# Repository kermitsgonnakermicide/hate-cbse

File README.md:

# hate-cbse
A desk-sized CoreXY pen plotter with a custom RP2350 based motherboard!

# why? 
### just why?
- i come from the great country of India, and as a result of that I'm in CBSE [(Central Board of Secondary Education)](https://www.cbse.gov.in/)
- CBSE, being a central board(for the entire country) and in general being decades behind other boards/methods has some quirky little requirements which seem utterly useless to the average individual
- one of those requirements is to a 'practical file' for maths, physics, chemistry and biology - these files are supposed to detail every single experiment you do in the lab and their results
- while this has great intentions, it has become so bad that a 'lab manual' has been published and students are expected to copy it word for word(not even kidding there) including the results and submit it
- i went through this myself and now that i'm moving into 11th(junior year) and the volume of experiments shoots straight up, I need a solution to this horrid problem

for additional context, please view this [youtube video](https://www.youtube.com/watch?v=U_G3jSLx4hc)
## enter, the hatecbse plotter
- this is an awesome corexy plotter that has about 300x300 mm of usable space, good enough for all my sheets and stuff
- its frame is built with 20x20 aluminium extrusion and is powered by NEMA17 stepper motors 
- while I initially thought I would skip on making a full on PCB for this project, you only hackclub once so I decided to make my own, printer motherboard-esque concotion around an RP2350B and the TMC2209 steppers(sticking with the breakout boards for that one purely because of cost)
- firmware wise, i'm not smart enough to write CNC plotter firmware so I'm using grblHAL, an opensource piece of firmware for all kinds of CNC plotters - you can check out Firmware/ for my config and and firmware file

# setup guide
- print and assemble the PCB(personally, i'm skipping all THT components for JLC assembly including a couple caps and resistors because I have them at home and they're for imp stuff(would appreciate being able to swap them out))
- print all files in production/Prints (quantity is indicated in the filename)
- assemble the frame(you will need a lot of T nuts for the alumnium extrusions)
- mount the PCB backplate, the motor holders + motor, belt guide
- assemble the toolhead and its profile, along with its linear actuator
- route your timing belts through center, motor pulley and ends

> use this image for reference!
- put PCB on backplate, wire servos, steppers and limit switches to the board and anything else you want to add(I exposed a lot of power and I2C pins)
- give it USB power and 12v 5A power from your favourite power source(personally using my benchtop powersupply, but you could use anything)
- flash firmware and get to plotting!

# note for reviewer(s)
this project will be partially self funded out of sheer necessity, so please do not be concerned about any excess BOM cost

# Images

> full render

>PCB render

> routed PCB

> cleaned up schematic

# Zine

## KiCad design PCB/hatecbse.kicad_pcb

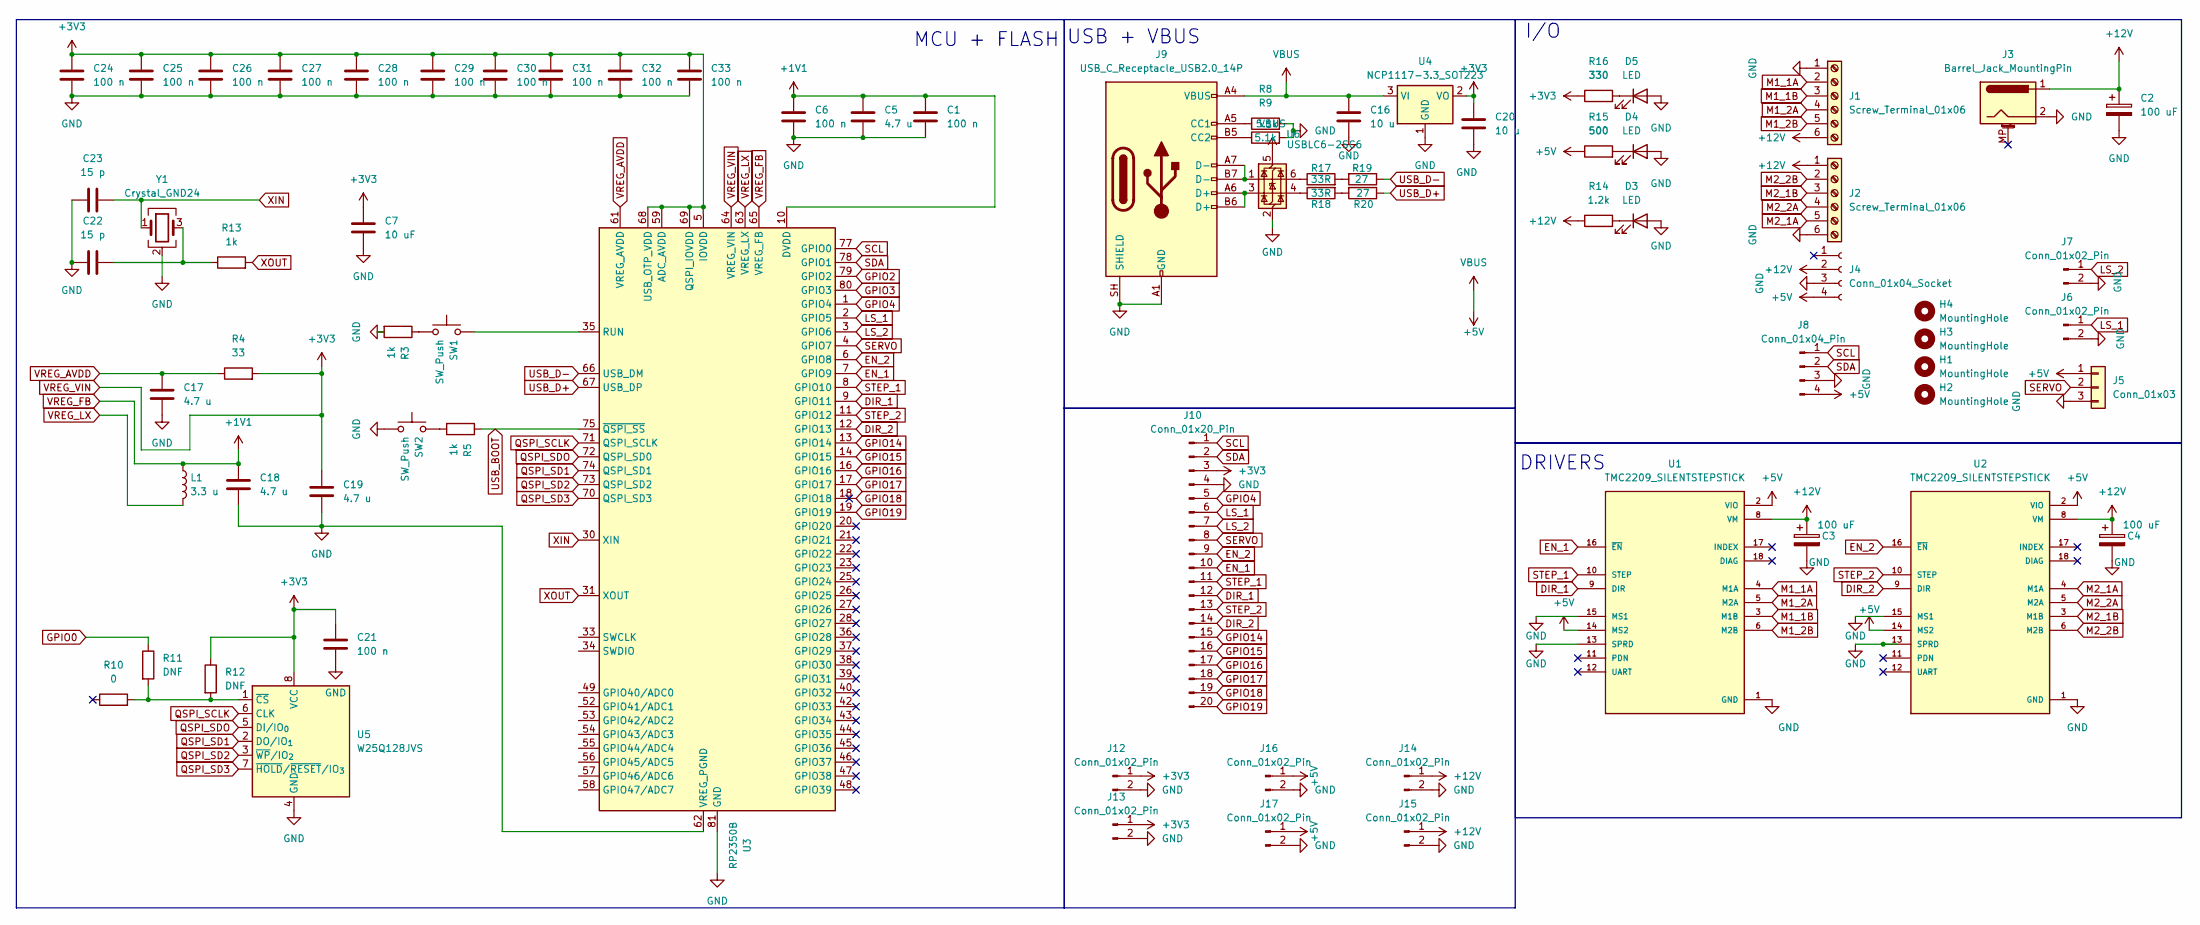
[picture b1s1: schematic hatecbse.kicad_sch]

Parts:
C1, C6, C21, C24, C25, C26, C27, C28, C29, C30, C31, C32, C33: 100 n; C_0402_1005Metric
C2, C3, C4: 100 uF; CP_Radial_D4.0mm_P1.50mm
C5, C17, C18, C19: 4.7 u; C_0402_1005Metric
C7: 10 uF; C_0402_1005Metric
C16, C20: 10 u; C_0402_1005Metric
C22, C23: 15 p; C_0402_1005Metric
D3, D4, D5: LED; LED_D3.0mm
H1, H2, H3, H4: MountingHole; MountingHole_3.2mm_M3
J1, J2: Screw_Terminal_01x06; PhoenixContact_MSTBA_2,5_6-G_1x06_P5.00mm_Horizontal
J3: Barrel_Jack_MountingPin; BarrelJack_CUI_PJ-063AH_Horizontal
J4: Conn_01x04_Socket; PinSocket_1x04_P2.54mm_Vertical
J5: Conn_01x03; PinHeader_1x03_P2.54mm_Vertical
J6, J7: Conn_01x02_Pin; PinHeader_1x02_P2.54mm_Vertical
J8: Conn_01x04_Pin; PinHeader_1x04_P2.54mm_Vertical
J9: USB_C_Receptacle_USB2.0_14P; USB_C_Receptacle_XKB_U262-16XN-4BVC11
J10: Conn_01x20_Pin; PinSocket_1x20_P2.54mm_Vertical
J12, J13, J14, J15, J16, J17: Conn_01x02_Pin; PinSocket_1x02_P2.54mm_Vertical
L1: 3.3 u; L_0805_2012Metric
R3, R5, R13: 1k; R_0402_1005Metric
R4: 33; R_0201_0603Metric
R8, R9: 5.1k; R_0603_1608Metric
R10: 0; R_0805_2012Metric
R11, R12: DNF
R14: 1.2k; R_Axial_DIN0204_L3.6mm_D1.6mm_P1.90mm_Vertical
R15: 500; R_Axial_DIN0204_L3.6mm_D1.6mm_P1.90mm_Vertical
R16: 330; R_Axial_DIN0204_L3.6mm_D1.6mm_P1.90mm_Vertical
R17, R18: 33R; R_0402_1005Metric; LCSC C25105
R19, R20: 27; R_0201_0603Metric
SW1, SW2: SW_Push; SW_Tactile_SPST_NO_Straight_CK_PTS636Sx25SMTRLFS
U1, U2: TMC2209_SILENTSTEPSTICK; MODULE_TMC2209_SILENTSTEPSTICK; PARTREV 1.20
U3: RP2350B; QFN-80-1EP_10x10mm_P0.4mm_EP3.4x3.4mm
U4: NCP1117-3.3_SOT223; SOT-223-3_TabPin2
U5: W25Q128JVS; SOIC-8_5.3x5.3mm_P1.27mm
U6: USBLC6-2SC6; SOT-23-6; LCSC C5180249
Y1: Crystal_GND24; Crystal_SMD_Abracon_ABM8G-4Pin_3.2x2.5mm

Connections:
+5V: C16.1, J4.4, J5.1, J8.4, J9.A4 (VBUS), J9.A9 (VBUS), J9.B4 (VBUS), J9.B9 (VBUS), J16.1, J17.1, R15.1, U1.2 (VIO), U1.14 (MS2), U2.2 (VIO), U2.14 (MS2), U4.3 (VI), U6.5 (VBUS)
+12V: C2.1, C3.1, C4.1, J1.6, J2.1, J3.1, J4.2, J14.1, J15.1, R14.1, U1.8 (VM), U2.8 (VM)
DIR_1: J10.12, U1.9 (DIR), U3.9 (GPIO11)
DIR_2: J10.14, U2.9 (DIR), U3.12 (GPIO13)
EN_1: J10.10, U1.16 (~EN), U3.7 (GPIO9)
EN_2: J10.9, U2.16 (~EN), U3.6 (GPIO8)
GND: C1.2, C2.2, C3.2, C4.2, C5.2, C6.2, C7.2, C16.2, C17.1, C18.2, C19.2, C20.2, C21.2, C22.1, C23.1, C24.2, C25.2, C26.2, C27.2, C28.2, C29.2, C30.2, C31.2, C32.2, C33.2, D3.2 (A), D4.2 (A), D5.2 (A), J1.1, J2.6, J3.2, J4.3, J5.3, J6.2, J7.2, J8.3, J9.A1 (GND), J9.A12 (GND), J9.B1 (GND), J9.B12 (GND), J9.SH (SHIELD), J10.4, J12.2, J13.2, J14.2, J15.2, J16.2, J17.2, R3.2, R8.2, R9.2, SW2.1, U1.1 (GND), U1.7 (GND), U1.13 (SPRD), U1.15 (MS1), U2.1 (GND), U2.7 (GND), U2.13 (SPRD), U2.15 (MS1), U3.62 (VREG_PGND), U3.81 (GND), U4.1 (GND), U5.4 (GND), U6.2 (GND), Y1.2 (G), Y1.4 (G)
GPIO2: U3.79 (GPIO2)
GPIO3: U3.80 (GPIO3)
GPIO4: J10.5, U3.1 (GPIO4)
GPIO14: J10.15, U3.13 (GPIO14)
GPIO15: J10.16, U3.14 (GPIO15)
GPIO16: J10.17, U3.16 (GPIO16)
GPIO17: J10.18, U3.17 (GPIO17)
GPIO18: J10.19, U3.18 (GPIO18)
GPIO19: J10.20, U3.19 (GPIO19)
LS_1: J6.1, J10.6, U3.2 (GPIO5)
LS_2: J7.1, J10.7, U3.3 (GPIO6)
M1_1A: J1.2, U1.4 (M1A)
M1_1B: J1.3, U1.3 (M1B)
M1_2A: J1.4, U1.5 (M2A)
M1_2B: J1.5, U1.6 (M2B)
M2_1A: J2.5, U2.4 (M1A)
M2_1B: J2.3, U2.3 (M1B)
M2_2A: J2.4, U2.5 (M2A)
M2_2B: J2.2, U2.6 (M2B)
unnamed: C22.2, R13.1, Y1.3
unnamed: D3.1 (K), R14.2
unnamed: D4.1 (K), R15.2
unnamed: D5.1 (K), R16.2
unnamed: J9.A5 (CC1), R8.1
unnamed: J9.B5 (CC2), R9.1
unnamed: J9.A6 (D+), J9.B6 (D+), U6.3 (I/O2)
unnamed: J9.A7 (D-), J9.B7 (D-), U6.1 (I/O1)
unnamed: R3.1, SW1.1
unnamed: R5.2, SW2.2
unnamed: R17.1, U6.6 (I/O1)
unnamed: R17.2, R19.2
unnamed: R18.1, U6.4 (I/O2)
unnamed: R18.2, R20.2
unnamed: SW1.2, U3.35 (RUN)
unnamed: R10.2, R11.2, R12.2, U5.1 (~CS)
QSPI_SCLK: U3.71 (QSPI_SCLK), U5.6 (CLK)
QSPI_SD1: U3.74 (QSPI_SD1), U5.2 (DO/IO_{1})
QSPI_SD2: U3.73 (QSPI_SD2), U5.3 (~WP/IO_{2})
QSPI_SD3: U3.70 (QSPI_SD3), U5.7 (~HOLD/~RESET/IO_{3})
QSPI_SDO: U3.72 (QSPI_SD0), U5.5 (DI/IO_{0})
SCL: J8.1, J10.1, U3.77 (GPIO0)
SDA: J8.2, J10.2, U3.78 (GPIO1)
SERVO: J5.2, J10.8, U3.4 (GPIO7)
STEP_1: J10.11, U1.10 (STEP), U3.8 (GPIO10)
STEP_2: J10.13, U2.10 (STEP), U3.11 (GPIO12)
USB_BOOT: R5.1, U3.75 (~QSPI_SS)
USB_D+: R20.1, U3.67 (USB_DP)
USB_D-: R19.1, U3.66 (USB_DM)
VREG_AVDD: C17.2, R4.1, U3.61 (VREG_AVDD)
VREG_FB: C1.1, C5.1, C6.1, C18.1, L1.1, U3.10 (DVDD), U3.32 (DVDD), U3.51 (DVDD), U3.65 (VREG_FB)
VREG_LX: L1.2, U3.63 (VREG_LX)
VREG_VIN: C7.1, C19.1, C20.1, C21.1, C24.1, C25.1, C26.1, C27.1, C28.1, C29.1, C30.1, C31.1, C32.1, C33.1, J10.3, J12.1, J13.1, R4.2, R12.1, R16.1, U3.5 (IOVDD), U3.15 (IOVDD), U3.24 (IOVDD), U3.29 (IOVDD), U3.41 (IOVDD), U3.50 (IOVDD), U3.59 (ADC_AVDD), U3.60 (IOVDD), U3.64 (VREG_VIN), U3.68 (USB_OTP_VDD), U3.69 (QSPI_IOVDD), U3.76 (IOVDD), U4.2 (VO), U5.8 (VCC)
XIN: C23.2, U3.30 (XIN), Y1.1
XOUT: R13.2, U3.31 (XOUT)

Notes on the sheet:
MCU + FLASH
DRIVERS
USB + VBUS
I/O

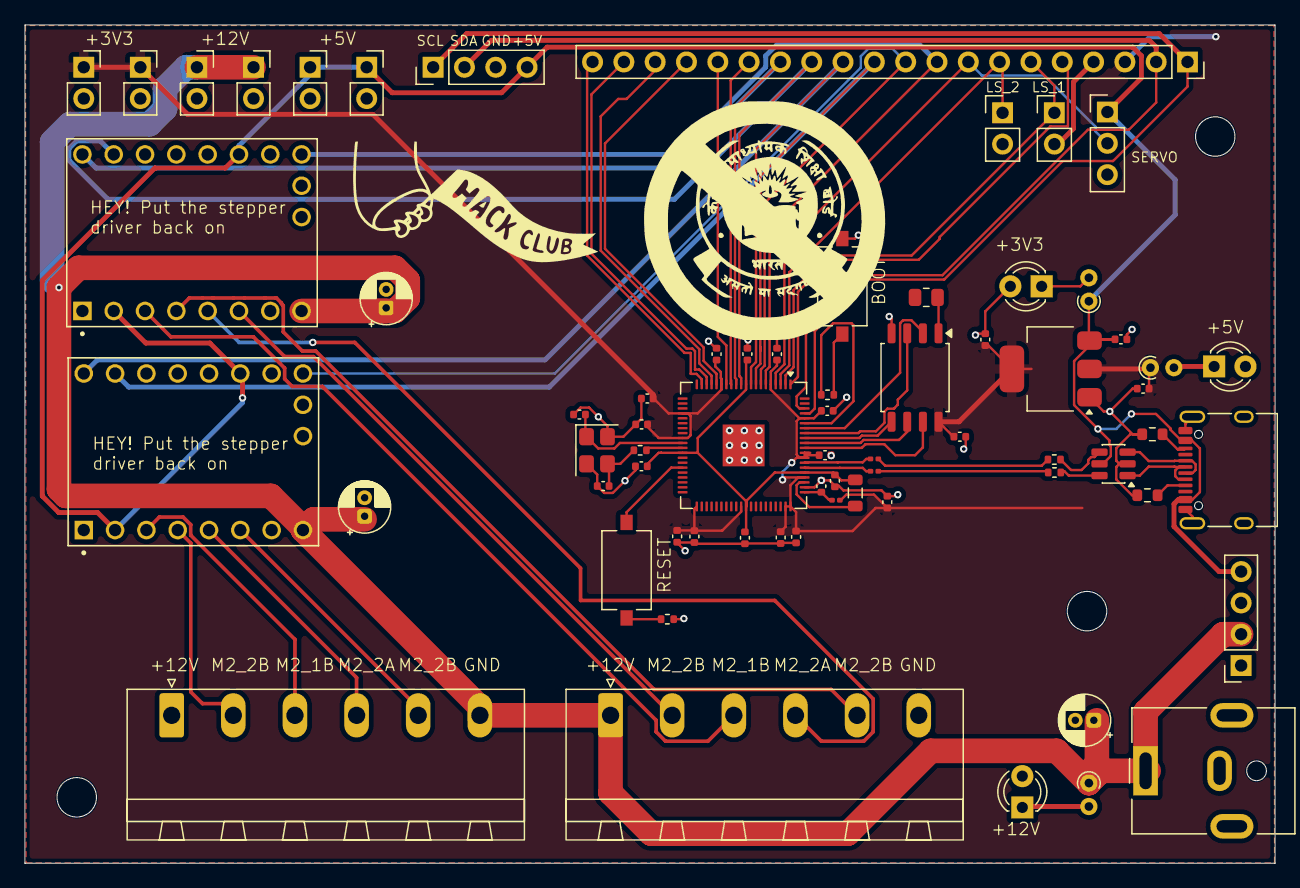
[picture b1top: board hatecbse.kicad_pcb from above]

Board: 4 copper layers, 101.4 x 68.0 mm, 71 parts (0 on the bottom side), 59 nets.

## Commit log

2026-05-19 first one
2026-05-27 diddy
2026-05-28 finally done with PCB
2026-05-28 update 3d files
2026-05-28 updates and some stuff
2026-05-28 full updates for everything
2026-05-28 final hardware commit
2026-05-28 update readme + firmware
2026-05-28 final commit
2026-05-28 oops
2026-05-29 updated render
2026-05-29 add BOM
2026-05-29 final zine
2026-05-29 final
2026-05-29 jiggu
2026-06-03 add TOTAL row to BOM
